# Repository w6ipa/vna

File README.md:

VNA Calibration and Testing PCB

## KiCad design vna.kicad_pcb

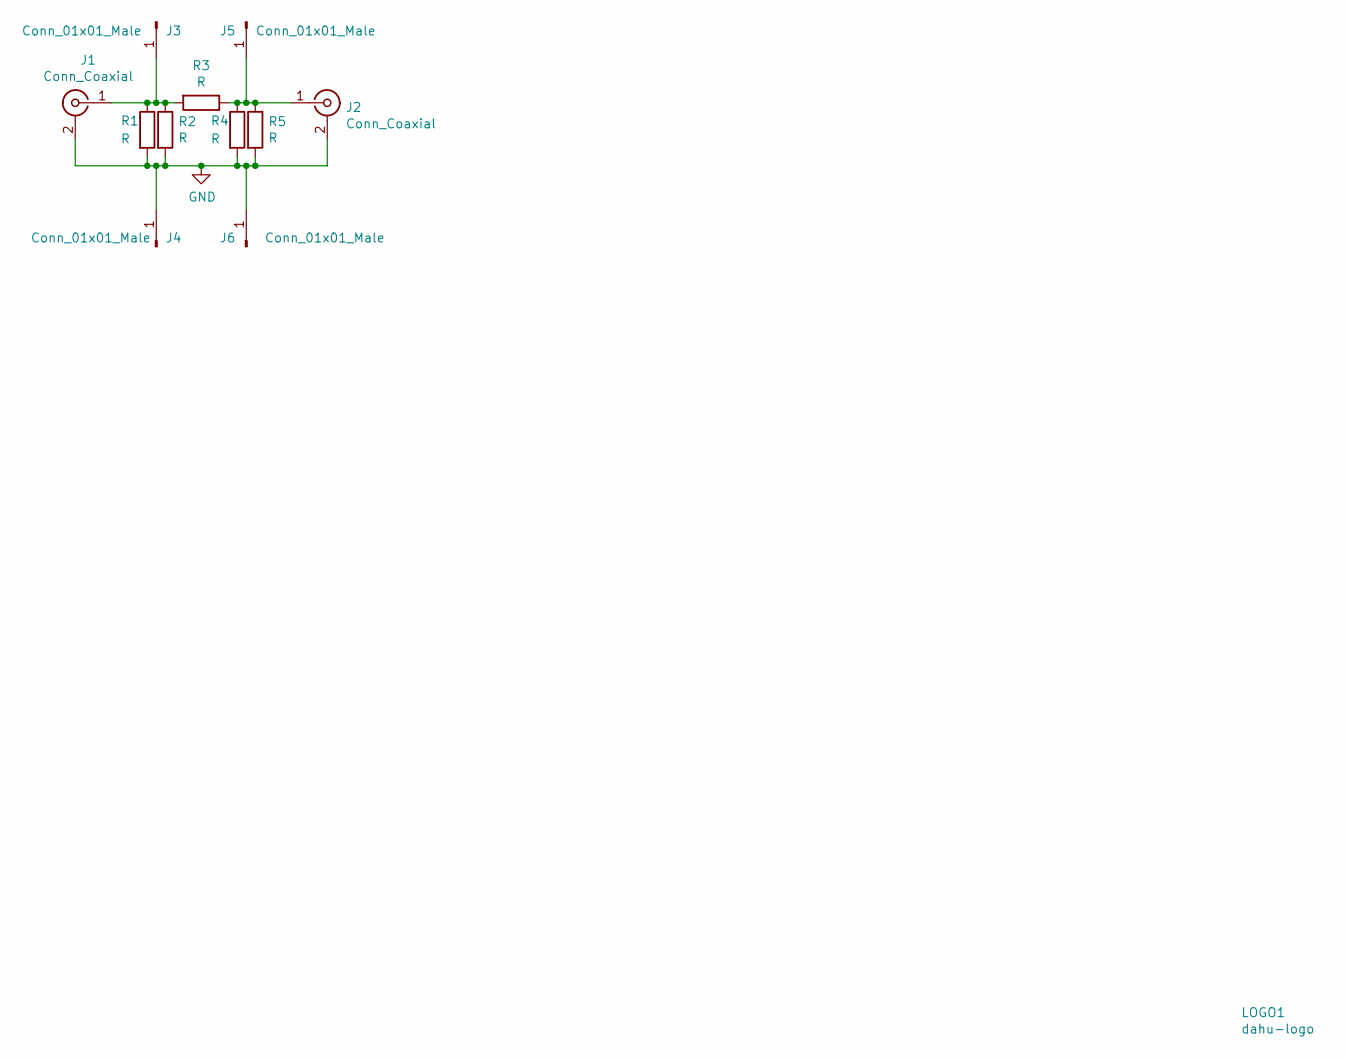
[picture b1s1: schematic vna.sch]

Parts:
J1, J2: Conn_Coaxial; SMA_EdgeMount_5mm
J3, J4, J5, J6: Conn_01x01_Male; SolderWirePad_1x01_Drill1.5mm
LOGO1: dahu-logo; W6IPA-Logo-9mmx8mm
R1, R2, R3, R4, R5: R; R_1206_3216Metric

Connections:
GND: J1.2 (Ext), J2.2 (Ext), J4.1, J6.1, R1.2, R2.2, R4.2, R5.2
unnamed: J1.1 (In), J3.1, R1.1, R2.1, R3.2
unnamed: J2.1 (In), J5.1, R3.1, R4.1, R5.1

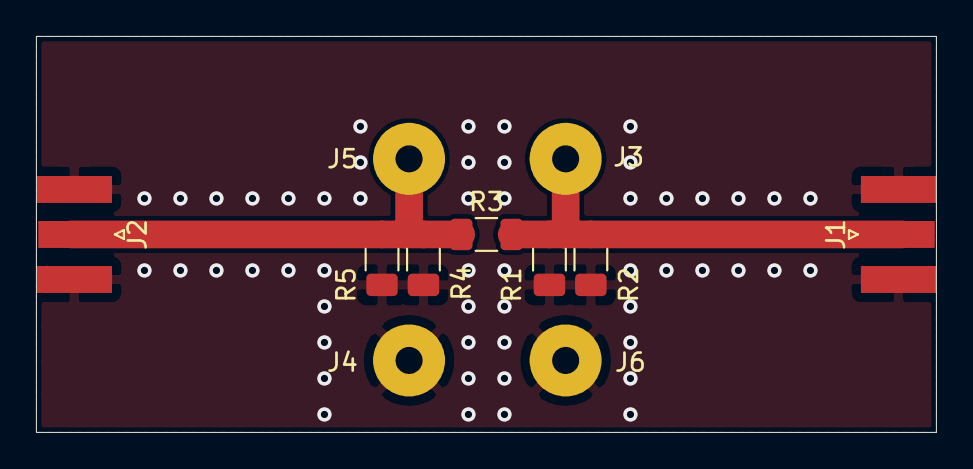
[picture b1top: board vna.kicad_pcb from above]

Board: 2 copper layers, 50.0 x 22.0 mm, 12 parts (1 on the bottom side), 3 nets.
